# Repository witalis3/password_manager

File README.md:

# password_manager
Na razie wszystko dosyć poufne.

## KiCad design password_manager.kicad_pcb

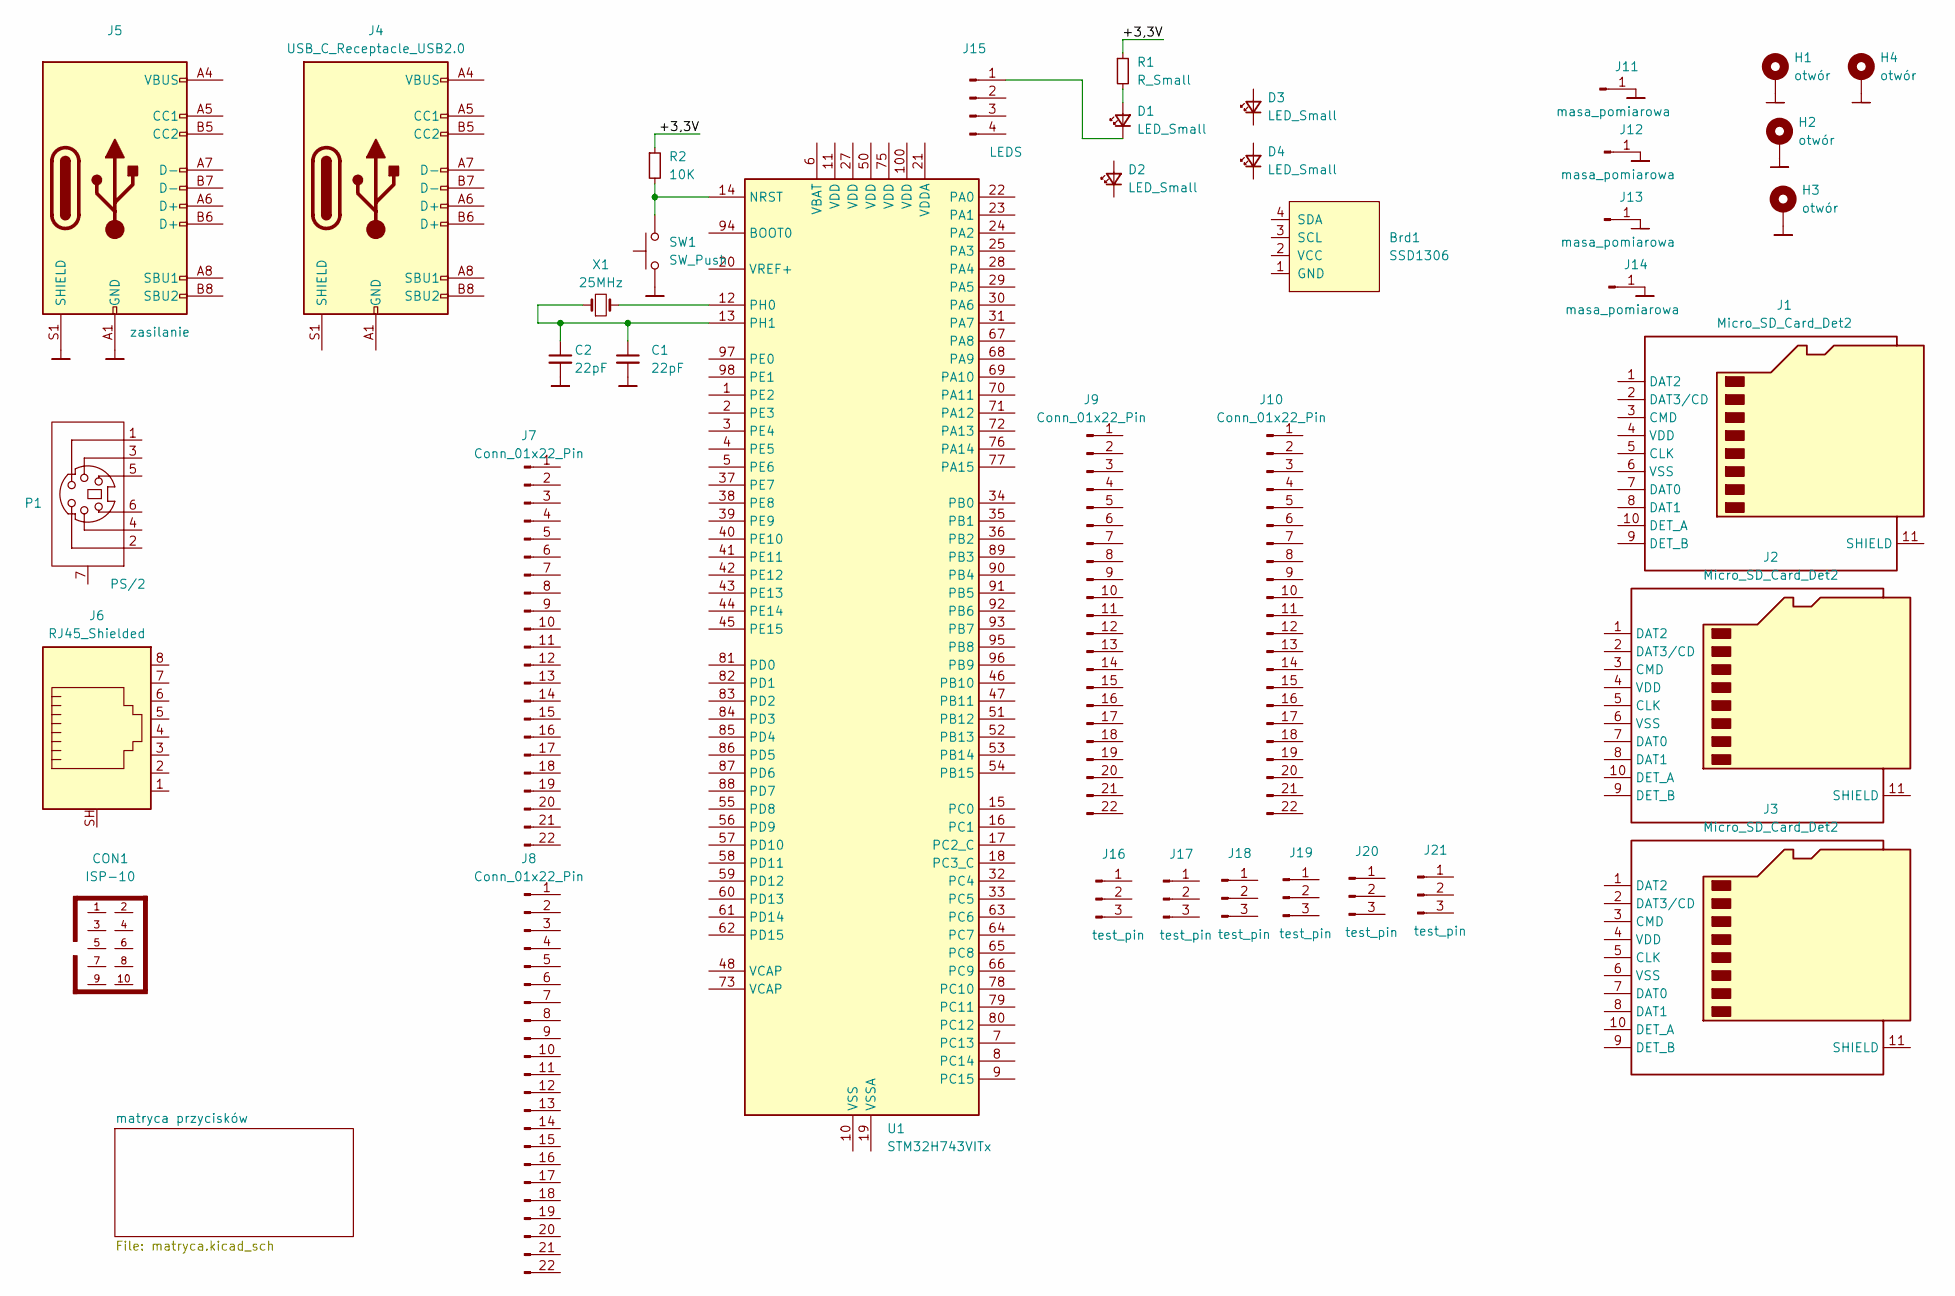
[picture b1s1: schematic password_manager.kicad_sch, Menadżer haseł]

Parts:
Brd1: SSD1306; 128x64OLED
C1, C2: 22pF; C_0805_2012Metric_Pad1.18x1.45mm_HandSolder
CON1: ISP-10; IDC-10_angled
D1, D2, D3, D4: LED_Small; D_0805_2012Metric_Pad1.15x1.40mm_HandSolder
H1, H2, H3, H4: otwór; MountingHole_3.2mm_M3_DIN965_Pad_TopBottom
J1, J2, J3: Micro_SD_Card_Det2; microSD_HC_Hirose_DM3BT-DSF-PEJS
J4: USB_C_Receptacle_USB2.0; USB_C_Receptacle_GCT_USB4105-xx-A_16P_TopMnt_Horizontal
J5: zasilanie; USB_C_Receptacle_GCT_USB4105-xx-A_16P_TopMnt_Horizontal
J6: RJ45_Shielded; RJ45_6339160-1_TE_Connectivity
J7, J8: Conn_01x22_Pin; PinHeader_1x22_P2.54mm_Horizontal
J9, J10: Conn_01x22_Pin; PinHeader_1x22_P2.54mm_Vertical
J11, J12, J13, J14: masa_pomiarowa
J15: LEDS; 4_PIN
J16, J17, J18, J19, J20, J21: test_pin; 3_PIN
P1: PS/2; Connector_Mini-DIN_Female_6Pin_2rows
R1: R_Small; R_0805_2012Metric_Pad1.20x1.40mm_HandSolder
R2: 10K; R_0805_2012Metric_Pad1.20x1.40mm_HandSolder
SW1: SW_Push; SW_Push_1P1T_NO_6x6mm_H9.5mm
U1: STM32H743VITx; LQFP-100_14x14mm_P0.5mm
X1: 25MHz; Crystal_SMD_5032-2Pin_5.0x3.2mm_HandSoldering

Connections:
/+3,3V: R1.1, R2.1
GND: C1.2, C2.2, H1.1, H2.1, H3.1, H4.1, J5.A1 (GND), J5.A12 (GND), J5.B1 (GND), J5.B12 (GND), J5.S1 (SHIELD), J11.1, J12.1, J13.1, J14.1, SW1.1
unnamed: D1.2 (A), R1.2
unnamed: D1.1 (K), J15.1
unnamed: J4.A1 (GND), J4.A12 (GND), J4.B1 (GND), J4.B12 (GND)
unnamed: J4.A4 (VBUS), J4.A9 (VBUS), J4.B4 (VBUS), J4.B9 (VBUS)
unnamed: J5.A4 (VBUS), J5.A9 (VBUS), J5.B4 (VBUS), J5.B9 (VBUS)
unnamed: R2.2, SW1.2, U1.14 (NRST)
unnamed: U1.12 (PH0), X1.2
unnamed: C1.1, C2.1, U1.13 (PH1), X1.1
unnamed: U1.10 (VSS), U1.26 (VSS), U1.49 (VSS), U1.74 (VSS), U1.99 (VSS)

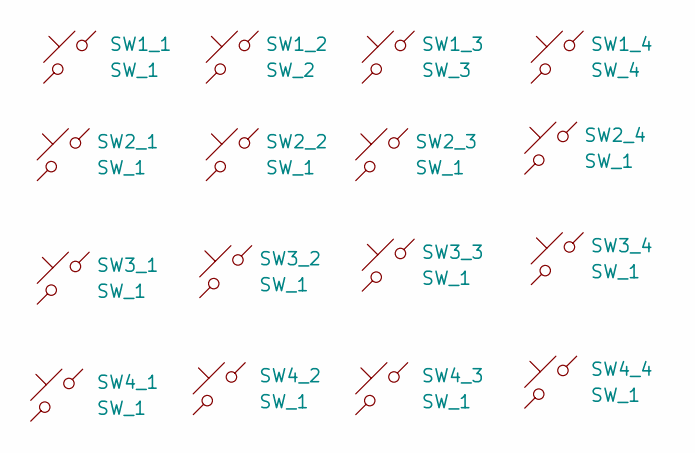
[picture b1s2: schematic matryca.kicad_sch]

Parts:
SW1_1, SW2_1, SW2_2, SW2_3, SW2_4, SW3_1, SW3_2, SW3_3, SW3_4, SW4_1, SW4_2, SW4_3, SW4_4: SW_1; SW_Push_1P1T_NO_6x6mm_H9.5mm
SW1_2: SW_2; SW_Push_1P1T_NO_6x6mm_H9.5mm
SW1_3: SW_3; SW_Push_1P1T_NO_6x6mm_H9.5mm
SW1_4: SW_4; SW_Push_1P1T_NO_6x6mm_H9.5mm

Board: 2 copper layers, 55 parts (9 on the bottom side), 11 nets, no tracks yet.

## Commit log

2023-12-01 nowe libs
2023-12-03 kolejne elementy
2023-12-03 footprint nowy
2024-04-16 kicad8
